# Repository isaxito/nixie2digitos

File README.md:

Esquematicos y codigo pedorro actual del reloj nixie de 2 digitos que diseñé con 2 tubos IN-12.
 El codigo por ahora solo es para que funcione pero está abierta la posibilidad de meterle varias cosas, usé el core del attiny85 este: https://github.com/SpenceKonde/ATTinyCore
### Fotolas
No soy bueno sacando fotos, no puedo hacer que se los tubos se vean tan hermosos como se ven en persona

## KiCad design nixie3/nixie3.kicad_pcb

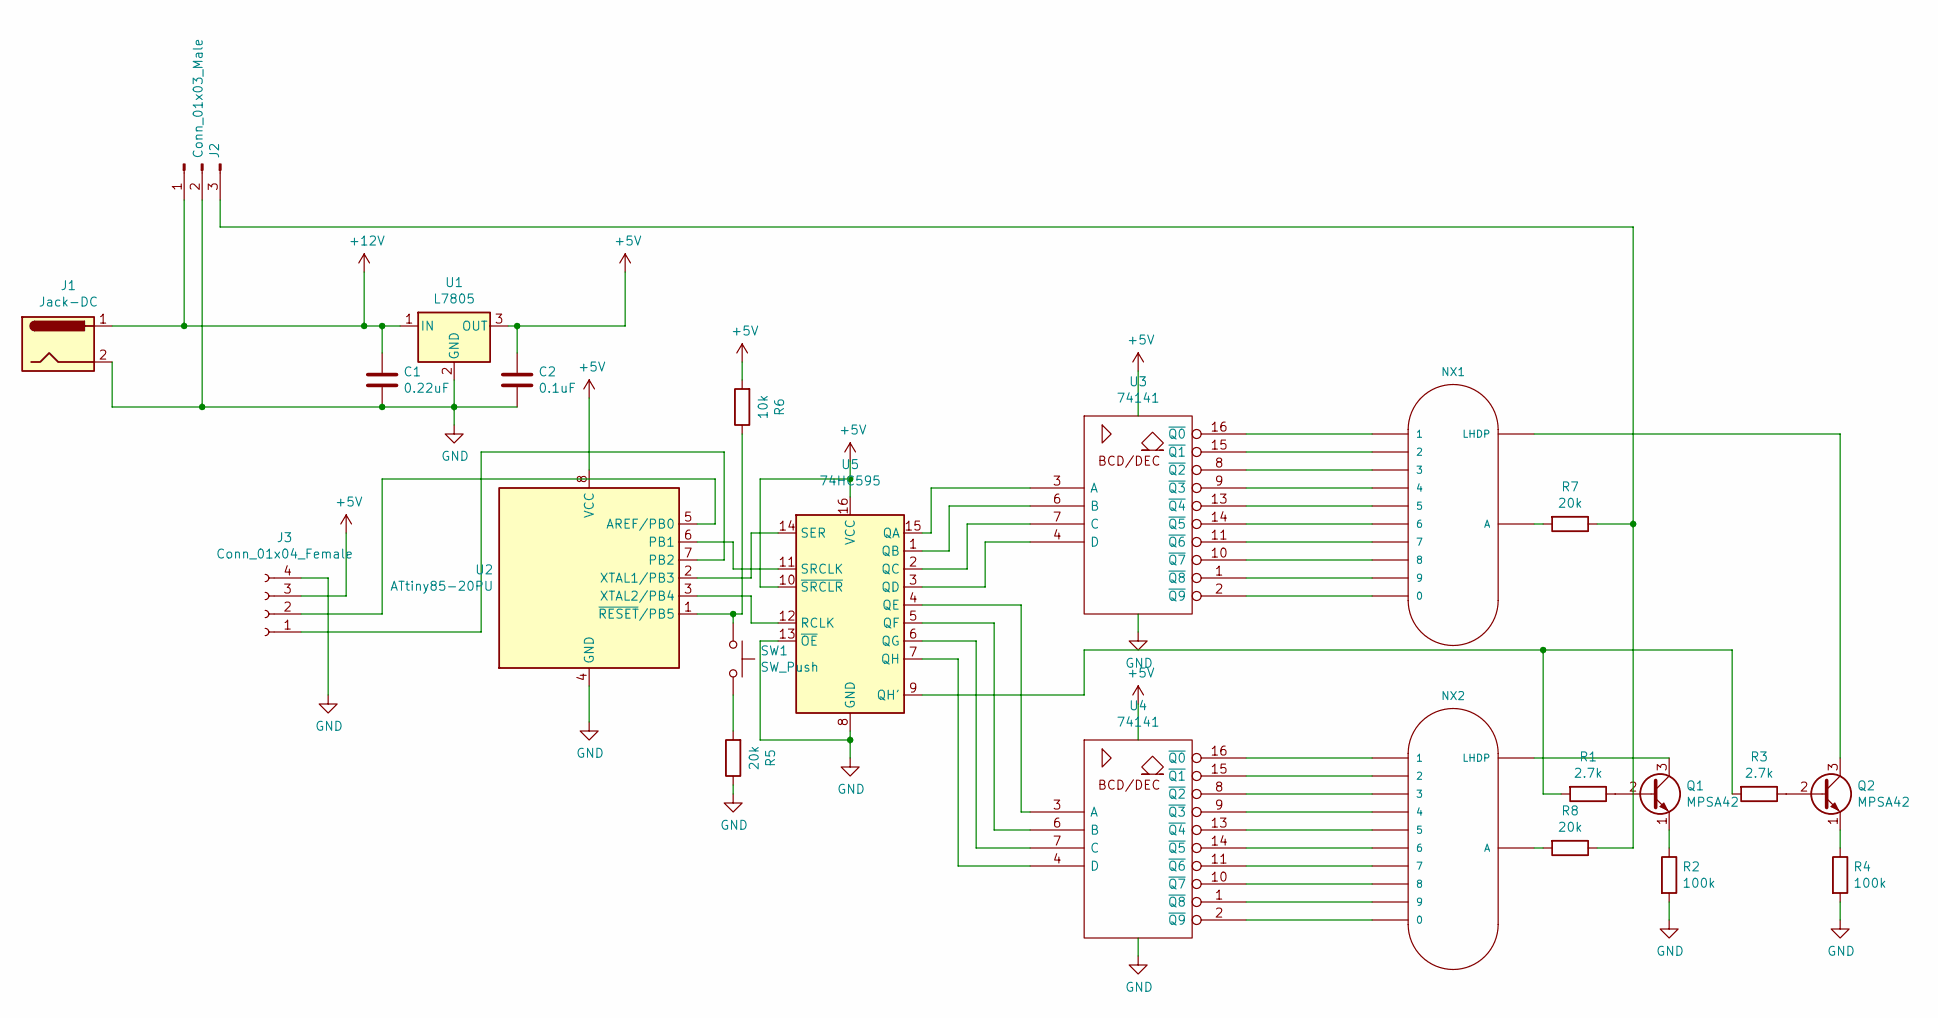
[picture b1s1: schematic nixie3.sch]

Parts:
C1: 0.22uF; C_Disc_D5.1mm_W3.2mm_P5.00mm
C2: 0.1uF; C_Disc_D5.1mm_W3.2mm_P5.00mm
J1: Jack-DC; BarrelJack_CUI_PJ-102AH_Horizontal
J2: Conn_01x03_Male; PinHeader_1x03_P2.54mm_Vertical
J3: Conn_01x04_Female; PinHeader_1x04_P2.54mm_Vertical
NX1, NX2: IN-12BORIGINAL; nixies-us-IN-12
Q1, Q2: MPSA42; TO-92_Inline_Wide
R1, R3: 2.7k; R_Axial_DIN0207_L6.3mm_D2.5mm_P7.62mm_Horizontal
R2, R4: 100k; R_Axial_DIN0207_L6.3mm_D2.5mm_P7.62mm_Horizontal
R5, R7, R8: 20k; R_Axial_DIN0207_L6.3mm_D2.5mm_P7.62mm_Horizontal
R6: 10k; R_Axial_DIN0207_L6.3mm_D2.5mm_P7.62mm_Horizontal
SW1: SW_Push; SW_PUSH_6mm_H5mm
U1: L7805; TO-220-3_Vertical
U2: ATtiny85-20PU; DIP-8_W7.62mm
U3, U4: 74141; DIP-16_W7.62mm
U5: 74HC595; DIP-16_W7.62mm

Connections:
+5V: C2.1, J3.3, R6.2, U1.3 (OUT), U2.8 (VCC), U3.5 (VCC), U4.5 (VCC), U5.10 (~SRCLR), U5.16 (VCC)
+12V: C1.1, J1.1, J2.1, U1.1 (IN)
GND: C1.2, C2.2, J1.2, J2.2, J3.4, R2.2, R4.2, R5.1, U1.2 (GND), U2.4 (GND), U3.12 (GND), U4.12 (GND), U5.8 (GND), U5.13 (~OE)
unnamed: J2.3, R7.1, R8.1
unnamed: J3.1, U2.7 (PB2)
unnamed: J3.2, U2.5 (AREF/PB0)
unnamed: NX1.0, U3.2 (~Q9)
unnamed: NX1.1, U3.16 (~Q0)
unnamed: NX1.2, U3.15 (~Q1)
unnamed: NX1.3, U3.8 (~Q2)
unnamed: NX1.4, U3.9 (~Q3)
unnamed: NX1.5, U3.13 (~Q4)
unnamed: NX1.6, U3.14 (~Q5)
unnamed: NX1.7, U3.11 (~Q6)
unnamed: NX1.8, U3.10 (~Q7)
unnamed: NX1.9, U3.1 (~Q8)
unnamed: NX1.A, R7.2
unnamed: NX1.LHDP, Q2.3 (C)
unnamed: NX2.0, U4.2 (~Q9)
unnamed: NX2.1, U4.16 (~Q0)
unnamed: NX2.2, U4.15 (~Q1)
unnamed: NX2.3, U4.8 (~Q2)
unnamed: NX2.4, U4.9 (~Q3)
unnamed: NX2.5, U4.13 (~Q4)
unnamed: NX2.6, U4.14 (~Q5)
unnamed: NX2.7, U4.11 (~Q6)
unnamed: NX2.8, U4.10 (~Q7)
unnamed: NX2.9, U4.1 (~Q8)
unnamed: NX2.A, R8.2
unnamed: NX2.LHDP, Q1.3 (C)
unnamed: Q1.1 (E), R2.1
unnamed: Q1.2 (B), R1.1
unnamed: Q2.1 (E), R4.1
unnamed: Q2.2 (B), R3.1
unnamed: R1.2, R3.2, U5.9 (QH')
unnamed: R5.2, SW1.2
unnamed: R6.1, SW1.1, U2.1 (~RESET~/PB5)
unnamed: U2.2 (XTAL1/PB3), U5.14 (SER)
unnamed: U2.3 (XTAL2/PB4), U5.12 (RCLK)
unnamed: U2.6 (PB1), U5.11 (SRCLK)
unnamed: U3.3 (A), U5.15 (QA)
unnamed: U3.4 (D), U5.3 (QD)
unnamed: U3.6 (B), U5.1 (QB)
unnamed: U3.7 (C), U5.2 (QC)
unnamed: U4.3 (A), U5.4 (QE)
unnamed: U4.4 (D), U5.7 (QH)
unnamed: U4.6 (B), U5.5 (QF)
unnamed: U4.7 (C), U5.6 (QG)

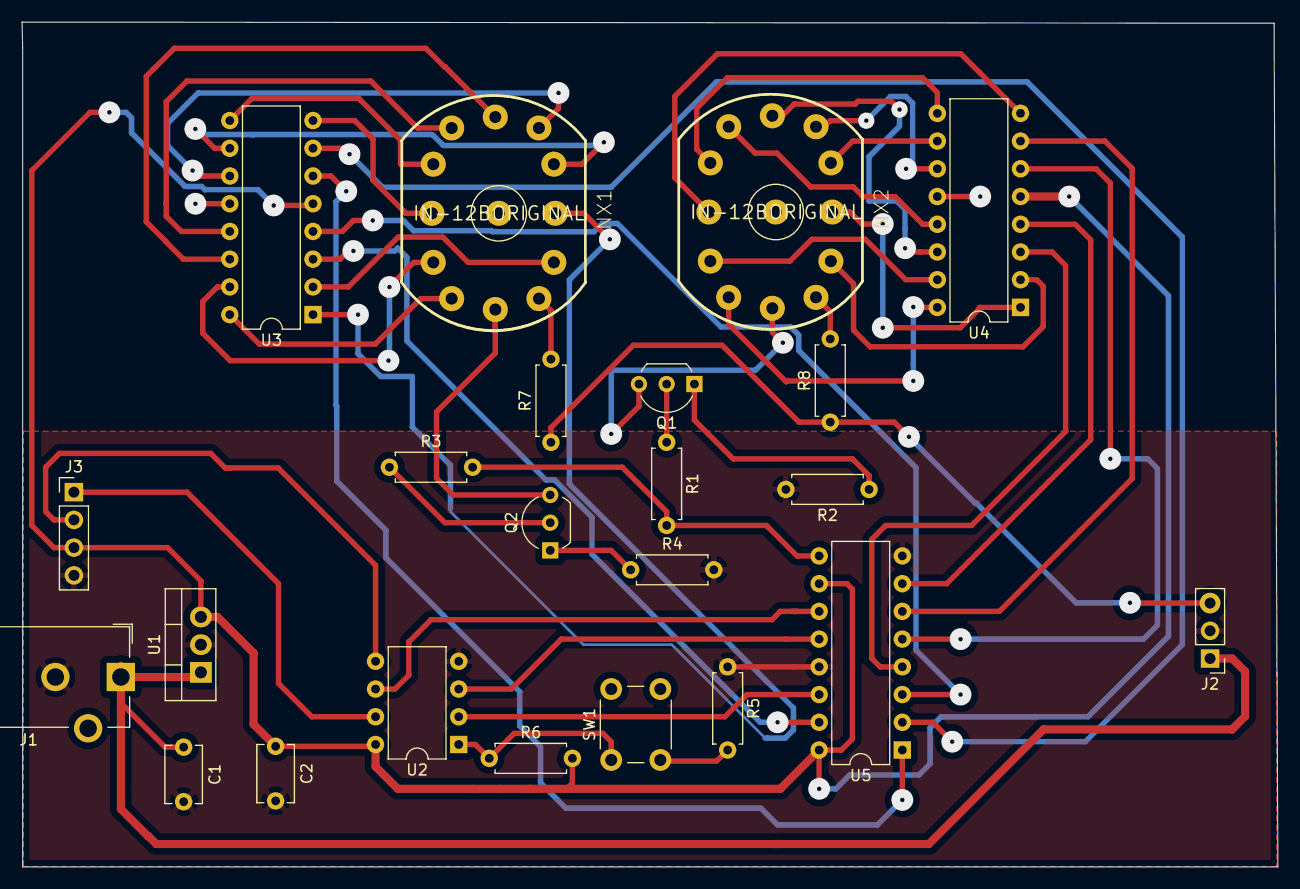
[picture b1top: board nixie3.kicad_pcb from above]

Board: 2 copper layers, 115.0 x 77.4 mm, 23 parts (0 on the bottom side), 48 nets.

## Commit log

2020-10-20 README actualizado
2020-10-21 Agregué fotos
2020-10-27 Fotos nuevas
